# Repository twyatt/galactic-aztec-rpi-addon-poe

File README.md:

# About

Custom Raspberry Pi Add-on board used as a PoE (power over ethernet) switch for the [Galactic Aztec] rocket. The board has a single Mini Fit Jr. port for PoE power input and 2 pairs of passthru ethernet ports that can have the PoE power toggled on/off.

Custom EagleCAD parts on this board can be found in the [SDSU Rocket Eagle Libraries].

## Wiring
The ethernet ports adhere to the following [10/100 mode B, DC on spares] wiring configuration:

| Pin | T568B Color  | Function |
|:---:|:------------:|:--------:|
| 1   | Orange/White | Rx +     |
| 2   | Orange       | Rx -     |
| 3   | Green/White  | Tx +     |
| 4   | Blue         | DC +     |
| 5   | Blue/White   | DC +     |
| 6   | Green        | Tx -     |
| 7   | Brown/White  | DC -     |
| 8   | Brown        | DC -     |

## Launch
For the [Galactic Aztec April 18th, 2015 launch], this board was used in conjunction with the [Galactic Aztec Raspberry Pi Add-on: Power] board to allow the rocket to be powered by external power provided by the ground station (conserving onboard battery power). Then during pre-launch sequence the PoE power was toggled off, thereby having the rocket use onboard battery power.

# Bill of Materials
| Qty | Name       | Description                          | Part Number          | Vendor   |
|:---:|:----------:|--------------------------------------|---------------------:|----------|
| 2   | RELAY[1,2] | Relay 5V 5A DPST-NC (2 Form B)       | [Z3640-ND]           | DigiKey  |
| 2   | Q1, Q2     | Transistor NPN 40V 600mA SOT-23-3    | [MMBT2222ATPMSCT-ND] | DigiKey  |
| 2   | R1, R2     | Resistor 1k 1/4W 1% 0603             | [RHM1.00KADCT-ND]    | DigiKey  |
| 2   | D1, D2     | Diode 50V 1A SOD-123                 | [SM4001PL-TPMSCT-ND] | DigiKey  |
| 4   | RJ45-[1-4] | Jack RJ45 CAT5/CAT5e                 | [380-1046-ND]        | DigiKey  |
| 1   |            | Molex Mini Fit Jr. 4-pos Right Angle | [WM1352-ND]          | DigiKey  |
| 2   | D3, D4     | LED Red Vf=1.8V If=2mA 0603          | [475-1195-2-ND]      | DigiKey  |
| 1   | R4         | Resistor 1.8kΩ 1/4W 1% 0603          | [P1.8KBYCT-ND]       | DigiKey  |
| 1   | R3         | Resistor 12kΩ 1/4W 1% 0603           | [RHM12.0KADCT-ND]    | DigiKey  |
| 1   |            | Header Stacking 2x20 Tall 23mm       | [1979]               | Adafruit |

[Galactic Aztec]: http://rocket.sdsu.edu/rockets
[SDSU Rocket Eagle Libraries]: https://github.com/twyatt/SDSURocket-Eagle-Libraries
[10/100 mode B, DC on spares]: https://en.wikipedia.org/wiki/Power_over_Ethernet#Pinouts
[Galactic Aztec April 18th, 2015 launch]: https://github.com/twyatt/galactic-aztec-launch-data
[Galactic Aztec Raspberry Pi Add-on: Power]: https://github.com/twyatt/galactic-aztec-rpi-addon-power
[Z3640-ND]: http://www.digikey.com/product-detail/en/G6B-2014P-US%20DC5/Z3640-ND/1815886
[MMBT2222ATPMSCT-ND]: http://www.digikey.com/product-detail/en/MMBT2222A-TP/MMBT2222ATPMSCT-ND/717394
[RHM1.00KADCT-ND]: http://www.digikey.com/product-detail/en/ESR03EZPF1001/RHM1.00KADCT-ND/1983752
[SM4001PL-TPMSCT-ND]: http://www.digikey.com/product-detail/en/SM4001PL-TP/SM4001PL-TPMSCT-ND/1793403
[380-1046-ND]: http://www.digikey.com/product-detail/en/SS-7188-NF/380-1046-ND/388308
[WM1352-ND]: http://www.digikey.com/product-search/en?x=0&y=0&lang=en&site=us&keywords=538-39-30-1040
[475-1195-2-ND]: http://www.digikey.com/product-detail/en/LS%20L29K-H1J2-1-Z/475-1195-1-ND/810356
[P1.8KBYCT-ND]: http://www.digikey.com/product-detail/en/ERJ-PA3F1801V/P1.8KBYCT-ND/5036145
[RHM12.0KADCT-ND]: http://www.digikey.com/product-detail/en/ESR03EZPF1202/RHM12.0KADCT-ND/1983756
[1979]: https://www.adafruit.com/product/1979

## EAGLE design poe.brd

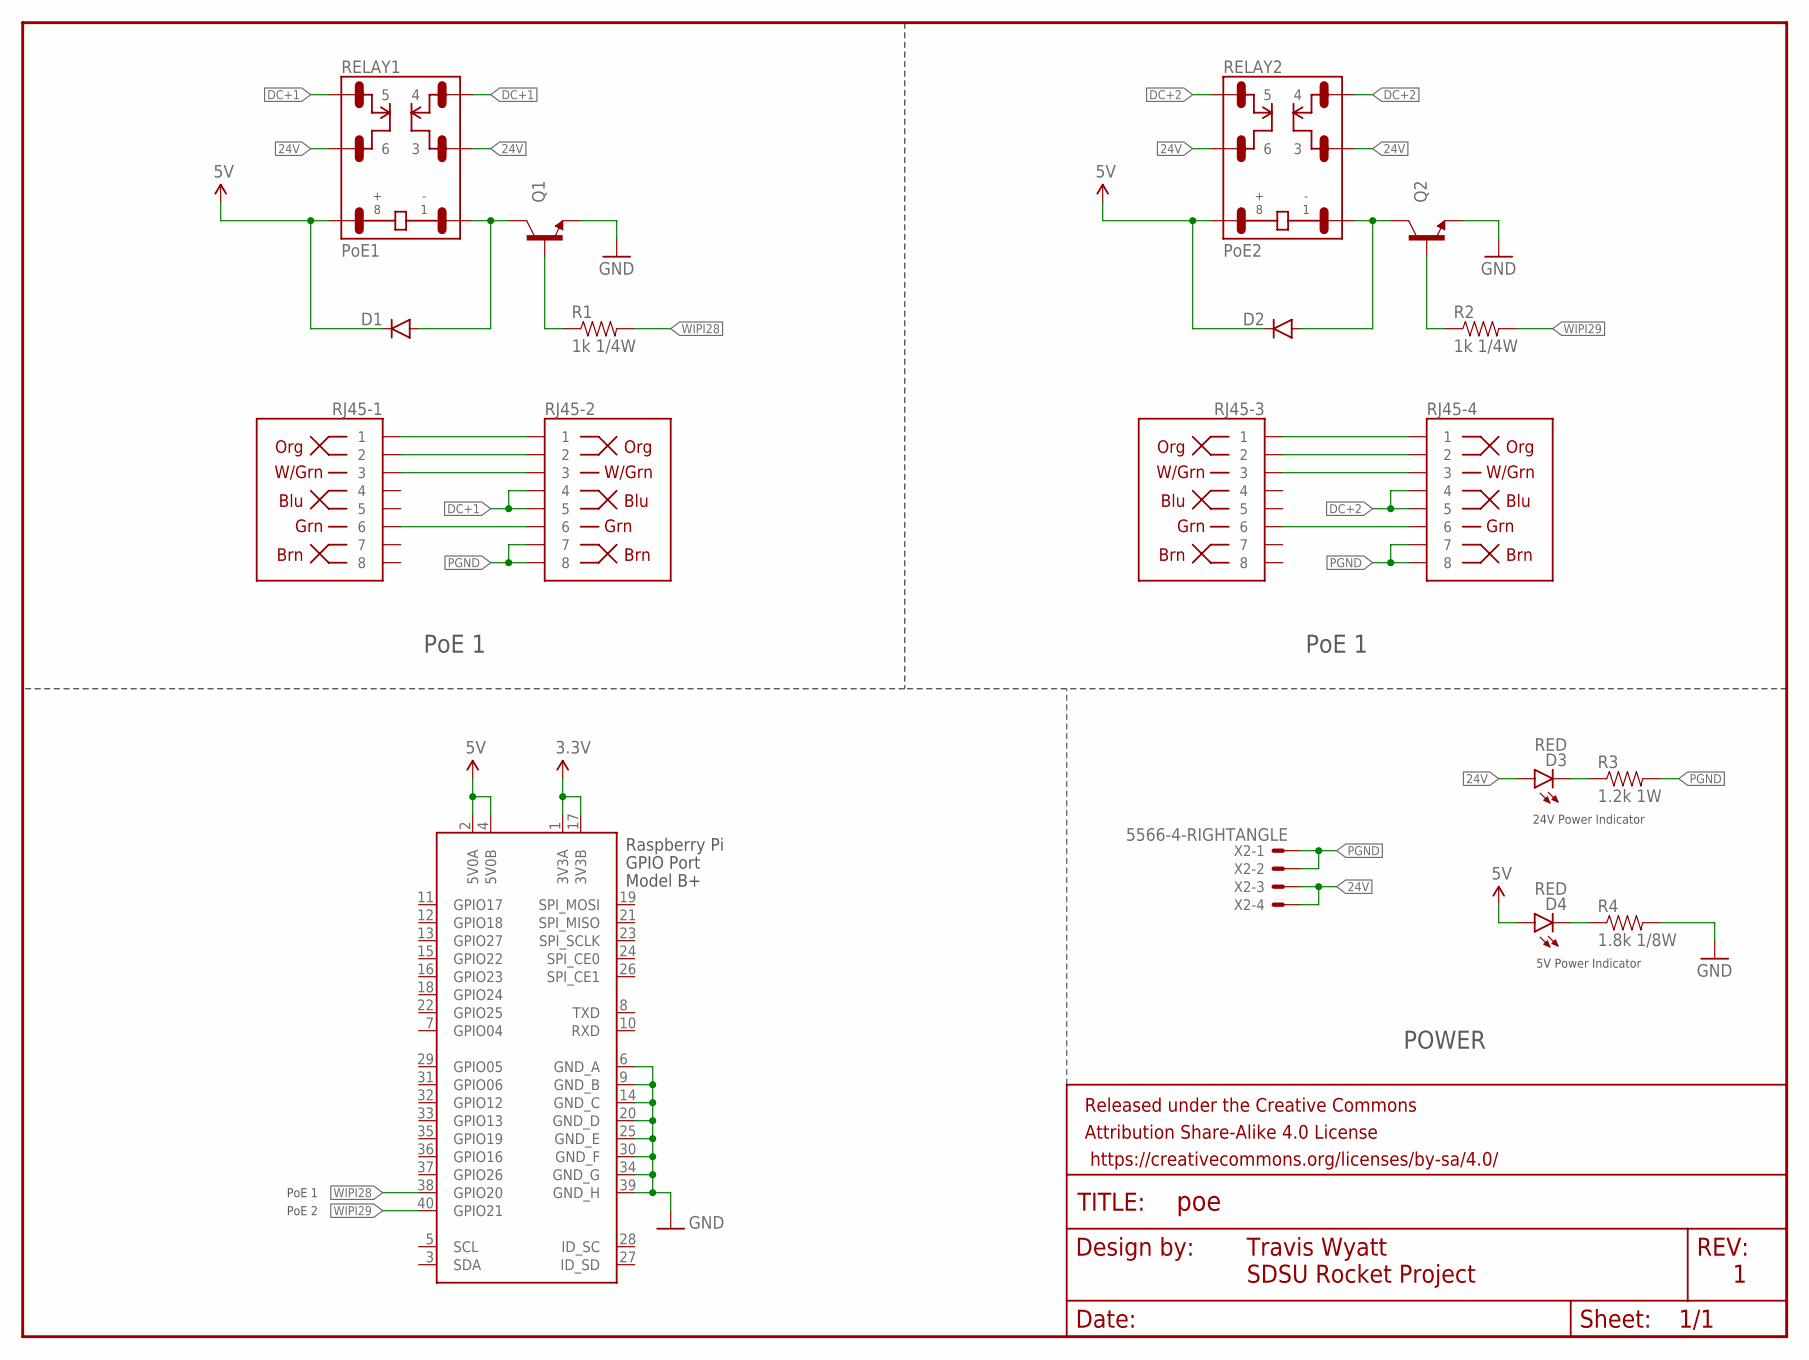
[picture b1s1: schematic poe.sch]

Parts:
D1, D2: DIODESOD123; SOD-123
D3, D4: RED; LED-0603
FRAME1: FRAME-LETTER; CREATIVE_COMMONS
Q1, Q2: TRANSISTOR_NPNSOT23-3; SOT23-3
R1, R2: 1k 1/4W; 0603-RES
R3: 1.2k 1W; R2512
R4: 1.8k 1/8W; 0603-RES
RELAY1: PoE1; G6B-2
RELAY2: PoE2; G6B-2
RJ45-1, RJ45-2, RJ45-3, RJ45-4: RJ45-8PTH; RJ45-8
X1: RASPI_BOARD_B+#_H; RASPI_BOARD_B+HAT
X2: 5566-4-RIGHTANGLE; 5566-4

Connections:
3.3V: X1.1 (3V3A), X1.17 (3V3B)
5V: D1.C, D2.C, D4.A, RELAY1.8, RELAY2.8, X1.2 (5V0A), X1.4 (5V0B)
24V: D3.A, RELAY1.3, RELAY1.6, RELAY2.3, RELAY2.6, X2.3, X2.4
DC+1: RELAY1.4, RELAY1.5, RJ45-2.4, RJ45-2.5
DC+2: RELAY2.4, RELAY2.5, RJ45-4.4, RJ45-4.5
GND: Q1.2 (E), Q2.2 (E), R4.2, X1.6 (GND_A), X1.9 (GND_B), X1.14 (GND_C), X1.20 (GND_D), X1.25 (GND_E), X1.30 (GND_F), X1.34 (GND_G), X1.39 (GND_H)
unnamed: Q1.1 (B), R1.1
unnamed: D1.A, Q1.3 (C), RELAY1.1
unnamed: D3.C, R3.1
unnamed: D4.C, R4.1
unnamed: D2.A, Q2.3 (C), RELAY2.1
unnamed: Q2.1 (B), R2.1
unnamed: RJ45-1.1, RJ45-2.1
unnamed: RJ45-1.2, RJ45-2.2
unnamed: RJ45-1.3, RJ45-2.3
unnamed: RJ45-1.6, RJ45-2.6
unnamed: RJ45-3.1, RJ45-4.1
unnamed: RJ45-3.2, RJ45-4.2
unnamed: RJ45-3.3, RJ45-4.3
unnamed: RJ45-3.6, RJ45-4.6
PGND: R3.2, RJ45-2.7, RJ45-2.8, RJ45-4.7, RJ45-4.8, X2.1, X2.2
WIPI28: R1.2, X1.38 (GPIO20)
WIPI29: R2.2, X1.40 (GPIO21)

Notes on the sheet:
PoE 1
POWER
Travis Wyatt
SDSU Rocket Project
24V Power Indicator
5V Power Indicator
PoE 2

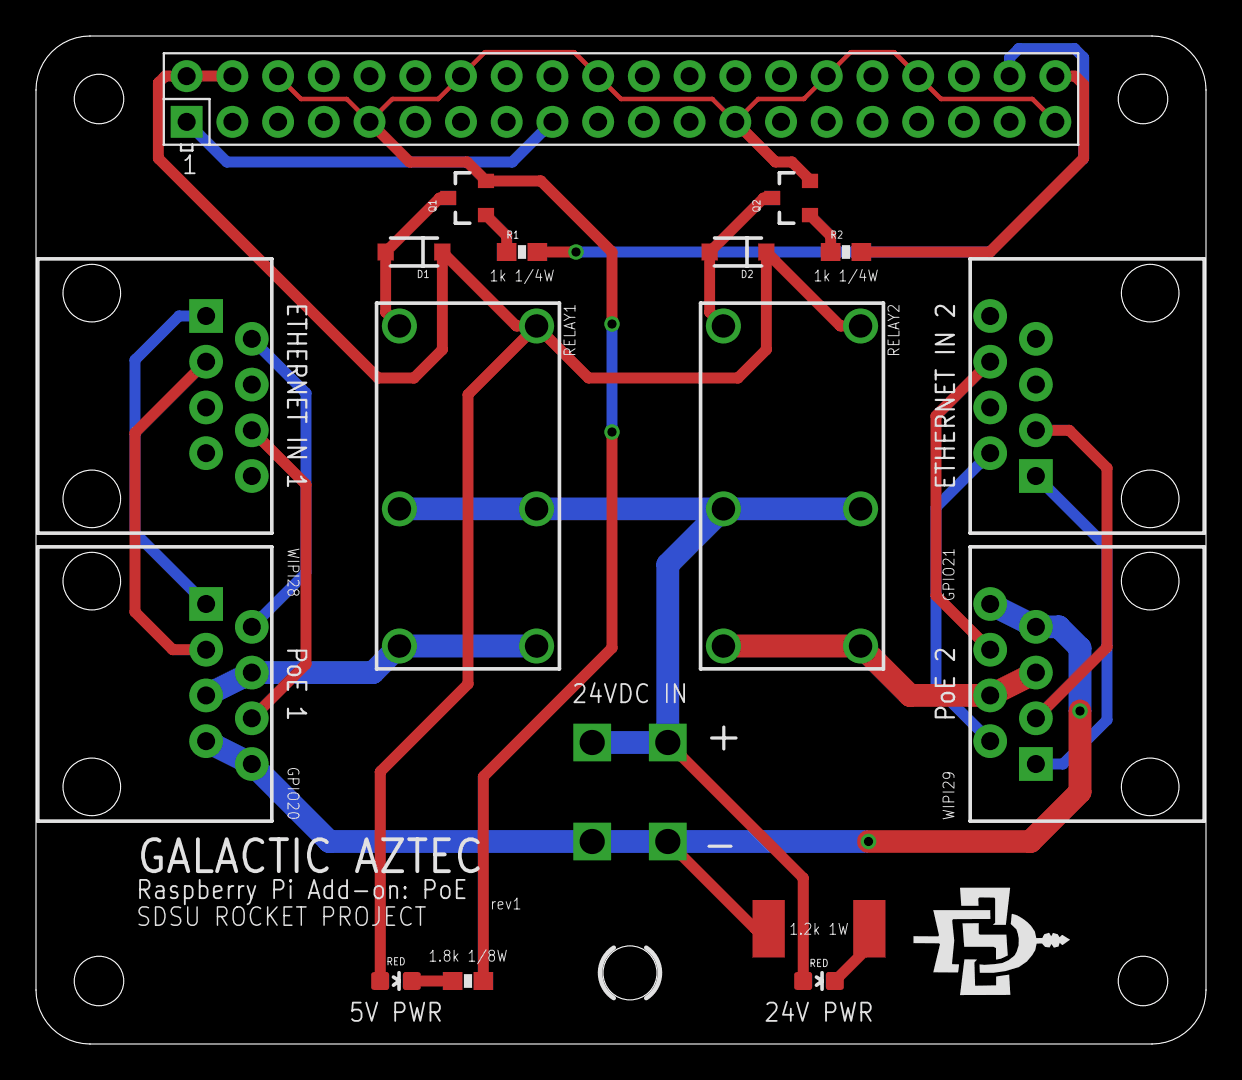
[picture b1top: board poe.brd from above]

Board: 2 copper layers, 65.0 x 56.0 mm, 19 parts (0 on the bottom side), 23 nets.

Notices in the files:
parts and their libraries:
SparkFun-DiscreteSemi: Licensing: Creative Commons ShareAlike 4.0 International - https://creativecommons.org/licenses/by-sa/4.0
SparkFun-Aesthetics: Released under the Creative Commons Attribution Share-Alike 4.0 License
SparkFun-Aesthetics: https://creativecommons.org/licenses/by-sa/4.0
